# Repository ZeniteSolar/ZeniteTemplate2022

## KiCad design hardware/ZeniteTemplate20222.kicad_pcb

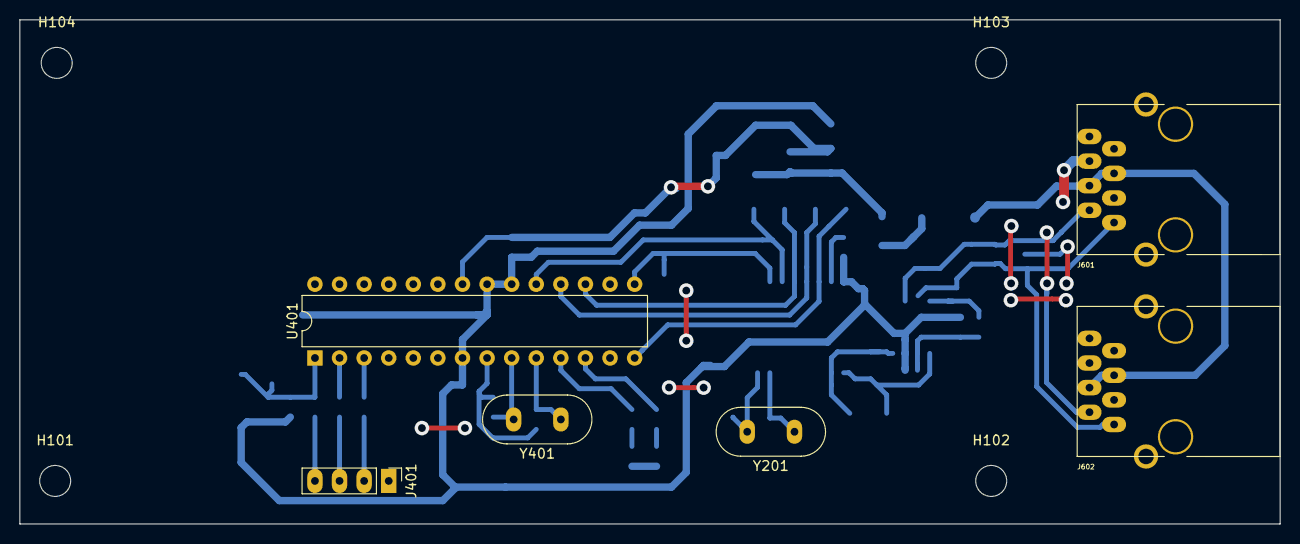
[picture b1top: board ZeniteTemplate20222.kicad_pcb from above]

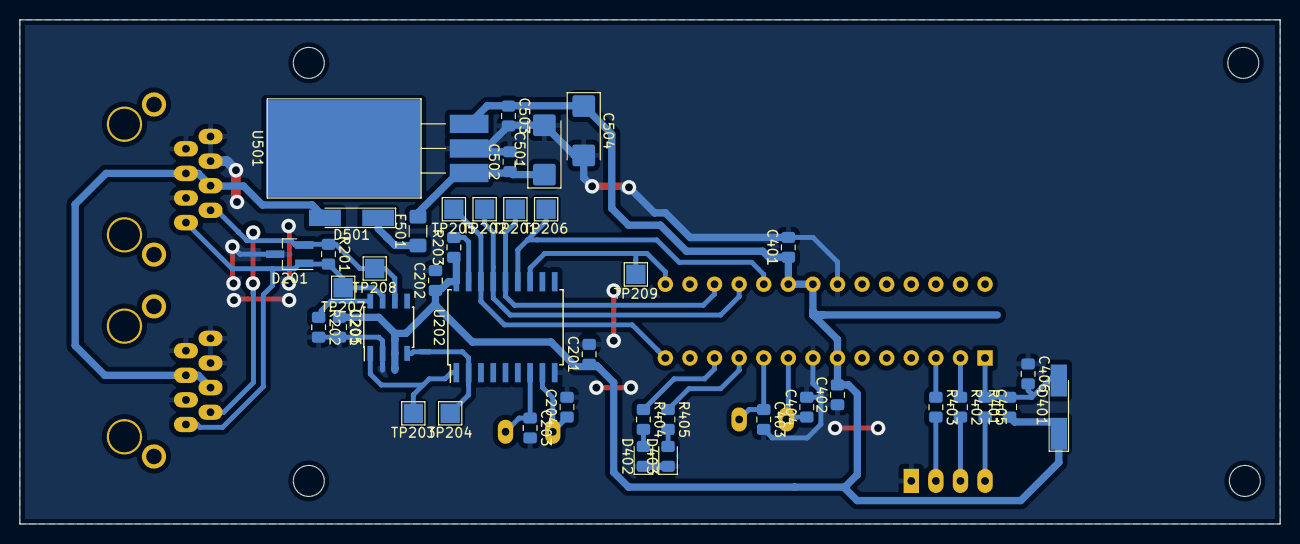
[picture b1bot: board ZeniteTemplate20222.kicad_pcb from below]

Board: 2 copper layers, 130.2 x 52.1 mm, 51 parts (41 on the bottom side), 30 nets.

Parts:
C201, C202, C205, C401, C402, C405, C406, C502, C503: 100nF; C_0805_2012Metric_Pad1.15x1.40mm_HandSolder
C203, C204, C403, C404: 22pF; C_0805_2012Metric_Pad1.15x1.40mm_HandSolder
C501, C504: 1uF; CP_EIA-6032-20_AVX-F_Pad2.25x2.35mm_HandSolder
D201: pesd1can; SOT-23_Handsoldering
D401, D501: LL4148; D_MiniMELF_Handsoldering
D402, D403: LED_RED; LED_0805_2012Metric_Pad1.15x1.40mm_HandSolder
F501: 500mA; Fuse_1206_3216Metric_Pad1.42x1.75mm_HandSolder
H101, H102, H103, H104: MountingHole; MountingHole_3.2mm_M3
J401: USART; PinHeader_1x04_P2.54mm_Vertical
J601, J602: RJ45; RJ45_YH59_01
R201: 120; R_0805_2012Metric_Pad1.15x1.40mm_HandSolder
R202: 4k7; R_0805_2012Metric_Pad1.15x1.40mm_HandSolder
R203, R401: 10k; R_0805_2012Metric_Pad1.15x1.40mm_HandSolder
R402, R403, R404, R405: 1k; R_0805_2012Metric_Pad1.15x1.40mm_HandSolder
TP201: SI; TestPoint_Pad_2.0x2.0mm
TP202: SO; TestPoint_Pad_2.0x2.0mm
TP203: TXCAN; TestPoint_Pad_2.0x2.0mm
TP204: RXCAN; TestPoint_Pad_2.0x2.0mm
TP205: SC; TestPoint_Pad_2.0x2.0mm
TP206: SCK; TestPoint_Pad_2.0x2.0mm
TP207: CAN_H; TestPoint_Pad_2.0x2.0mm
TP208: CAN_L; TestPoint_Pad_2.0x2.0mm
TP209: INT; TestPoint_Pad_2.0x2.0mm
U201: MCP2551-I/SN; SOIC-8_3.9x4.9mm_P1.27mm
U202: MCP2515-xSO; SOIC-18W_7.5x11.6mm_P1.27mm
U401: ATMEGA328P-PU; DIP-28_W7.62mm
U501: LM7805; TO-220-3_Horizontal_TabDown_SMD
Y201, Y401: 16MHz; Crystal_HC49-U_Vertical

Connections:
+5V: C201.1, C202.1, C205.1, C401.1, C402.2, C503.1, C504.1, D401.1 (K), R203.1, R401.1, U201.3 (VDD), U202.18 (VDD), U401.7 (VCC), U401.20 (AVCC), U401.21 (AREF), U501.3 (VO)
/CANBUS CONN/CAN_18V: D501.2 (A), J601.4, J601.5, J602.4, J602.5
/CANBUS CONN/CAN_H: D201.1 (A1), J601.1, J602.1, R201.2, TP207.1, U201.7 (CANH)
/CANBUS CONN/CAN_L: D201.2 (A2), J601.2, J602.2, R201.1, TP208.1, U201.6 (CANL)
/CANBUS/RXCAN: TP204.1, U201.4 (RXD), U202.2 (RXCAN)
/CANBUS/TXCAN: TP203.1, U201.1 (TXD), U202.1 (TXCAN)
/MCU/LED1: R405.1, U401.11 (PD5)
/MCU/LED2: R404.1, U401.12 (PD6)
/MCU/MCP_INT: TP209.1, U202.12 (~INT), U401.15 (PB1)
/MCU/MCP_SS: TP205.1, U202.16 (~CS), U401.14 (PB0)
/MCU/RESET: C405.1, C406.2, D401.2 (A), R401.2, U401.1 (~RESET/PC6)
/MCU/USART_RX: R402.1, U401.2 (PD0)
/MCU/USART_TX: R403.1, U401.3 (PD1)
/MISO: TP202.1, U202.15 (SO), U401.18 (PB4)
/MOSI: TP201.1, U202.14 (SI), U401.17 (PB3)
/POWER SUPPLY/+18V_OUT: C501.1, C502.1, F501.2, U501.1 (VI)
/SCK: TP206.1, U202.13 (SCK), U401.19 (PB5)
GND: C201.2, C202.2, C203.2, C204.2, C205.2, C401.2, C402.1, C403.2, C404.2, C406.1, C501.2, C502.2, C503.2, C504.2, D201.3 (common), D402.1 (K), D403.1 (K), J401.1, J601.3, J601.6, J601.7, J601.8, J602.3, J602.6, J602.7, J602.8, R202.2, U201.2 (VSS), U202.9 (VSS), U401.8 (GND), U401.22 (GND), U501.2 (GND)
unnamed: C203.1, U202.7 (OSC2), Y201.1
unnamed: C204.1, U202.8 (OSC1), Y201.2
unnamed: C403.1, U401.10 (XTAL2/PB7), Y401.1
unnamed: C404.1, U401.9 (XTAL1/PB6), Y401.2
unnamed: C405.2, J401.4
unnamed: D402.2 (A), R404.2
unnamed: D403.2 (A), R405.2
unnamed: D501.1 (K), F501.1
unnamed: J401.2, R403.2
unnamed: J401.3, R402.2
unnamed: R202.1, U201.8 (STBY)
unnamed: R203.2, U202.17 (~RESET)

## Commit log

2022-02-16 init template
2022-02-16 add gitignore licences and readme
2022-02-16 add templates configurations, rename files and clean
2022-02-16 fix template html
2022-02-16 remove hardware subdirectory
